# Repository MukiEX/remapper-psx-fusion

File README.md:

# Remapper PSX Fusion

An AI slop bodged combination of:

## HID Remapper

https://github.com/jfedor2/hid-remapper/

## usb-to-ps1-mouse-pro

https://github.com/Franticware/usb-to-ps1-mouse-pro

## Reasoning

USB-To-PS1-Mouse-Pro is a Pi Pico implementation of the PSX controller spec. It allows a USB mouse to work as a PlayStation mouse on a PSX console.

However, it does not work with non-standard mice, like the Taito Egret Ⅱ Mini Paddle and Trackball controller.

HID Remapper is a great Pi Pico project for converting one type of USB device to another type of USB device.

Originally, I had two RP2040 devices. One ran HID Remapper and one ran USB-To-PS1-Mouse-Pro.

At some point, I realized:

1. The USB-To-PS1-Mouse-Pro project uses one of the RP2040 cores to send PSX signals, and the other core to read the HID data.
2. The HID-Remapper project only uses one of the RP2040 cores, period.

The idea was simple: Replace the HID data reading from the first project with the remapper project.
What was less simple is that I'm definitely not capable of reading and gaining a thorough understanding of either project.

Despite the **incredibly** generous help of jfedor2, I couldn't get a solid handle of the HID Remapper, and beyond adding another build target to build it to Franticware's PSX adapter PCB, I could not get the device timing down, and the mouse movement was jittery and random at best. The project sat untouched for a couple years.

## Slop to the Rescue

A couple days ago I decided to take the dive and seeing if Claude could actually perform the project link that I couldn't figure out for the life of me. Two passes and 10 minutes later, it had a functioning patch. I rsynced it, and it completely failed to build. I removed Claude's CMake modification and restored my own, fixed it to match the constants and defintions that Claude wrote but never set properly, and about an hour later... it worked. Completely.

## PS360+

I also modified Franticware's PCB, which by default ends in a PSX controller connector, and replaced it with an RJ45 connector that was arranged to match the PS360+ pinout: https://filthypants.blogspot.com/2018/12/retro-console-rj45-pinouts-ps360-mc.html

Primary reason for this was that it was way easier to source RJ45 connectors and I had a few chopped off PSX controller cables, courtesy of Free Geek's room at 2DCon a few years ago: https://www.freegeektwincities.org/

The original, failed attempt technically worked fine with this PCB design, I just had to use two of them. One was flashed to the remapper_retro build I added to HID Remapper and the second was flashed to the PS1-Mouse-Pro. With the Claude merged version, I only had to flash the remapper_retro code and the Egret Mini adapter, properly converted into a Mouse, worked perfectly as a mouse on a PSX device.

## Modes

This version has had one major modification made over the original PS1-Mouse-Pro code: **it supports more than mice**.

The HID Remapper device modes present the PSX end as different devices:

- Switch - Presents as a PSX Dual Analog controller.
  - Home button toggles Analog button.
  - LED on device designates analog/digital modes, same as the original
- Stadia - Presents as a PSX NeGCon.
- Keyboard/Mouse - Presents as a PSX Mouse.

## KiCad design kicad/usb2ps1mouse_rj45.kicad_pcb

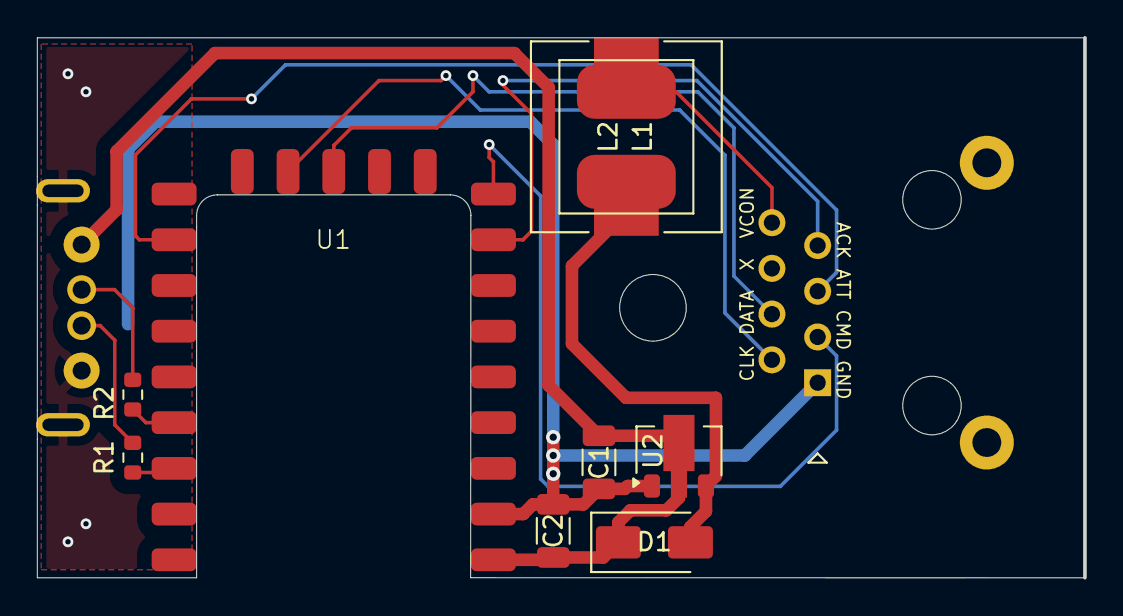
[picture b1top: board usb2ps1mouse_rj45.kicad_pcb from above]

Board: 2 copper layers, 58.2 x 30.0 mm, 11 parts (1 on the bottom side), 8 nets.

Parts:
C1, C2: 10u/16V; C_1206_3216Metric
D1: SS14; D_SMA
H1: MountingHole; MountingHole_3.7mm
J4: USB_A; USB_A_Sunken
L1: 220; L_10.4x10.4_H4.8
L2: 220; L_Sumida_CR75
R1, R2: 22R; R_0603_1608Metric
U1: RP2040-Zero
U2: ME2108A50PG; SOT-89-3

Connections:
+5V: C1.1, C2.1, D1.1 (K), J4.1 (VBUS), U1.23 (5V), U2.2 (Vout)
DM: J4.2 (D-), R2.1
DP: J4.3 (D+), R1.1
GND: C1.2, C2.2, J4.4 (GND), J4.5 (Shield), U1.22 (GND), U2.1 (Vss)
unnamed: D1.2 (A), L1.2, L2.2, U2.3 (Lx)
unnamed: R1.2, U1.3 (2)
unnamed: R2.2, U1.4 (3)
VCON: L1.1, L2.1
